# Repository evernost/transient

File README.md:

# transient
An analog synthesizer.

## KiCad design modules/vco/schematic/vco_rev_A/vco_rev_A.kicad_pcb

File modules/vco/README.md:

# VCO Module

Voltage-Controlled Module, with digital control for accurate tuning.

<!-- Example:
> This module implements a voltage-controlled low-pass filter based on a 4-pole ladder topology, intended for use in the analog signal path. -->

---

## Overview

- **Type:** VCO
- **Domain:** Analog, with Digital stabilisation
- **Status:** Work in progress

Block diagram: TODO!

---

## Features

- **Waveforms**: Sawtooth, Rectangular
- **Control**: exponential (1V/oct)
- **Inner Modulation**: up to 2 synchronised modulators to add more depth 
- **Sync**: digital input for synchronisation effect + random synchronisation

---

## Interfaces

### Inputs
| Name | Type | Range | Description |
|-----|------|-------|-------------|
| TODO | TODO | TODO |

### Outputs
| Name | Type | Description |
|------|------|-------------|
| TODO | TODO | TODO |

---

## Controls

| Control | Type | Description |
|--------|------|-------------|
| TODO | TODO | TODO |

---

## Electrical Characteristics

- **Supply voltage:** ±12V
- **Current consumption:** TBD mA
- **Signal levels:** TBD

---

## Implementation Notes

Design details, assumptions, or decisions worth remembering later.

Examples:
- Filter core based on [reference / paper / IC]
- Uses matched transistor pair for temperature stability
- Digital control smoothed with RC + oversampling

---

## Files

| File                  | Description                       |
|-----------------------|-----------------------------------|
| `vco_rev_A.pdf`       | Electrical schematic (PDF export) |
| `vco_rev_A.kicad_sch` | Schematic (KiCad 10.0.8)          |
| `vco_rev_A.kicad_pcb` | PCB layout (KiCad 10.0.8)|
| `firmware/`           | Embedded code for the VCO (STM32CubeIDE 2.1.1 - 2026) |

---

## Calibration / Tuning
> This section is TODO!

---

## Known Issues / TODO
- [ ] Create footprint for the STM32G441KB

---

## Revision History

| Revision | Date             | Notes                           |
|----------|------------------|---------------------------------|
| Rev A    | 10 November 2026 | Initial prototype               |
| Rev B    | TBA              | Added MCU for the tune control  |

---

## Related Modules

Links to other submodules in the repository:
- `../vca/`
- `../ring_modulator/`

---

## References
- Elektor FORMANT, Chapter 4 and 5

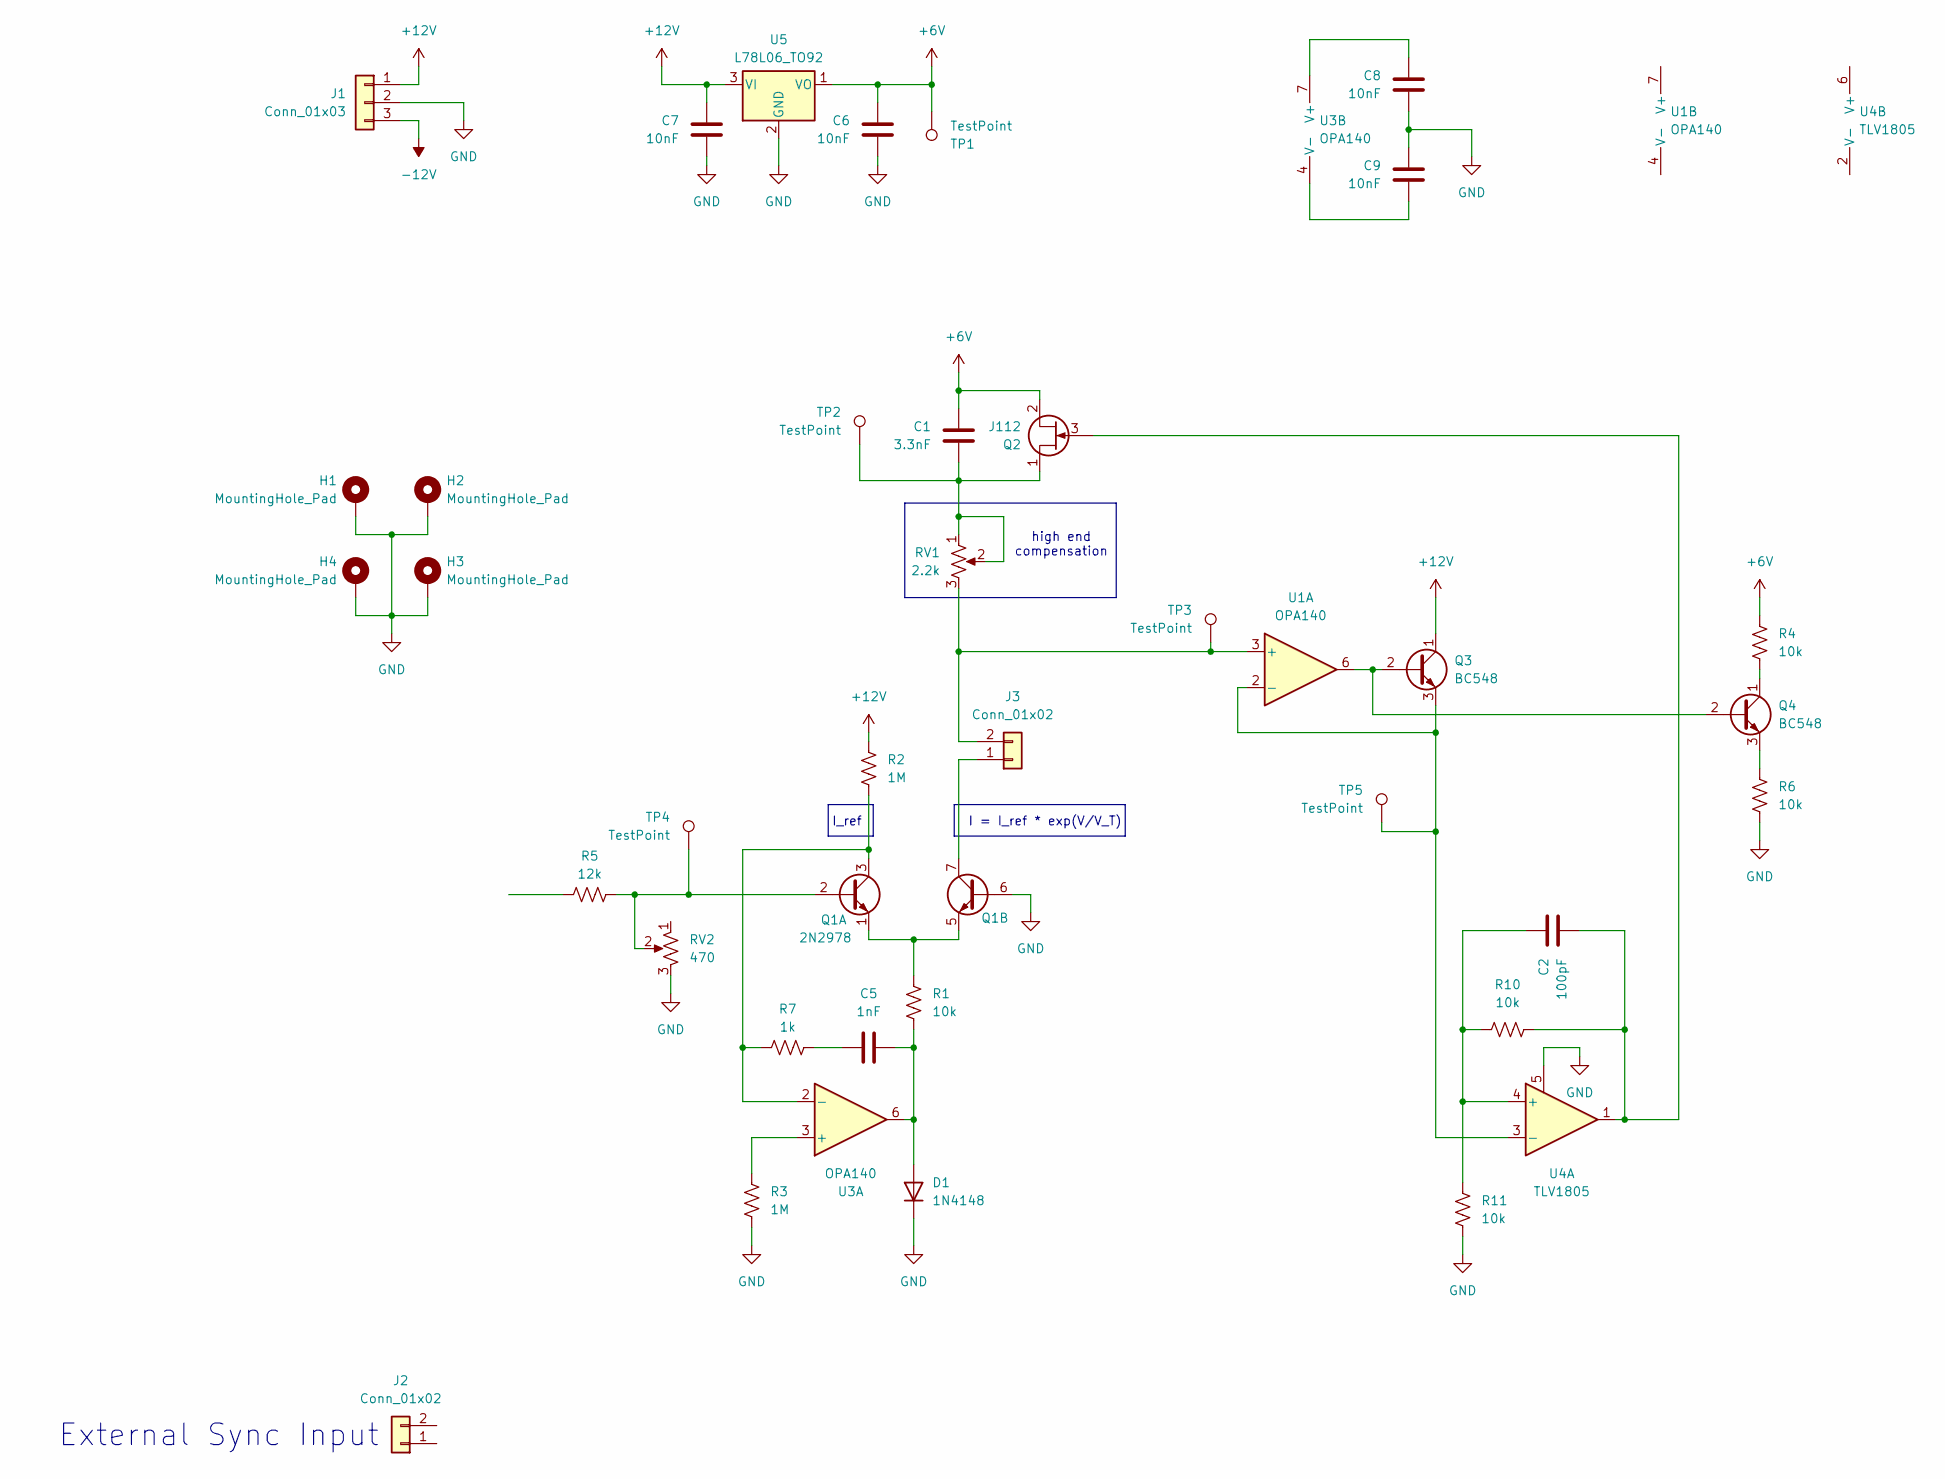
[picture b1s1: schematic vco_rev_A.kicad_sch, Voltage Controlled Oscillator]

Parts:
C1: 3.3nF; C_Rect_L7.0mm_W2.0mm_P5.00mm
C2: 100pF; C_Rect_L7.0mm_W2.0mm_P5.00mm
C5: 1nF; C_0805_2012Metric_Pad1.18x1.45mm_HandSolder
C6, C7, C8, C9: 10nF; C_Rect_L7.0mm_W2.0mm_P5.00mm
D1: 1N4148; D_DO-35_SOD27_P10.16mm_Horizontal
H1, H2, H3, H4: MountingHole_Pad; MountingHole_3.2mm_M3_Pad_Via
J1: Conn_01x03; WuerthElectronik_WR_TBL_Series_2545_1x03_P5.08mm_Horizontal
J2, J3: Conn_01x02; PinHeader_1x02_P2.54mm_Vertical
Q1: 2N2978; TO-5-6
Q2: J112; TO-92_Inline_Wide
Q3, Q4: BC548; TO-92L_Inline_Wide
R1, R4, R6, R10, R11: 10k; R_Axial_DIN0207_L6.3mm_D2.5mm_P10.16mm_Horizontal
R2, R3: 1M; R_Axial_DIN0207_L6.3mm_D2.5mm_P10.16mm_Horizontal
R5: 12k; R_Axial_DIN0207_L6.3mm_D2.5mm_P10.16mm_Horizontal
R7: 1k; R_Axial_DIN0207_L6.3mm_D2.5mm_P10.16mm_Horizontal
RV1: 2.2k; Potentiometer_Bourns_3296W_Vertical
RV2: 470; Potentiometer_Bourns_3296W_Vertical
TP1, TP2, TP3, TP4, TP5: TestPoint; TestPoint_Pad_D2.0mm
U1, U3: OPA140; VSSOP-8_3x3mm_P0.65mm
U4: TLV1805; SOT-23-6_Handsoldering
U5: L78L06_TO92; TO-92L_Inline_Wide

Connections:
+6V: C1.1, C6.1, Q2.2 (S), R4.1, TP1.1 (1_1), U5.1 (VO)
+12V: C7.1, J1.1, Q3.1 (C), R2.1, U5.3 (VI)
-12V: J1.3
GND: C6.2, C7.2, C8.2, C9.1, D1.1 (K), H1.1 (1_1), H2.1 (1_1), H3.1 (1_1), H4.1 (1_1), J1.2, Q1.6 (B2), R3.2, R6.2, R11.1, RV2.3, U4.5, U5.2 (GND)
unnamed: C5.1, R7.2
unnamed: C5.2, D1.2 (A), R1.2, U3.6
unnamed: J3.1, Q1.7 (C2)
unnamed: J3.2, RV1.3, TP3.1 (1_1), U1.3 (+)
unnamed: Q1.2 (B1), R5.2, RV2.2, TP4.1 (1_1)
unnamed: Q1.3 (C1), R2.2, R7.1, U3.2 (-)
unnamed: Q1.1 (E1), Q1.5 (E2), R1.1
unnamed: C1.2, Q2.1 (D), RV1.1, RV1.2, TP2.1 (1_1)
unnamed: C2.2, Q2.3 (G), R10.2, U4.1
unnamed: Q3.2 (B), Q4.2 (B), U1.6
unnamed: Q3.3 (E), TP5.1 (1_1), U1.2 (-), U4.3 (-)
unnamed: Q4.1 (C), R4.2
unnamed: Q4.3 (E), R6.1
unnamed: R3.1, U3.3 (+)
unnamed: C8.1, U3.7 (V+)
unnamed: C9.2, U3.4 (V-)
unnamed: C2.1, R10.1, R11.2, U4.4 (+)

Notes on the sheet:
I = I_ref * exp(V/V_T)
I_ref
high end compensation
External Sync Input

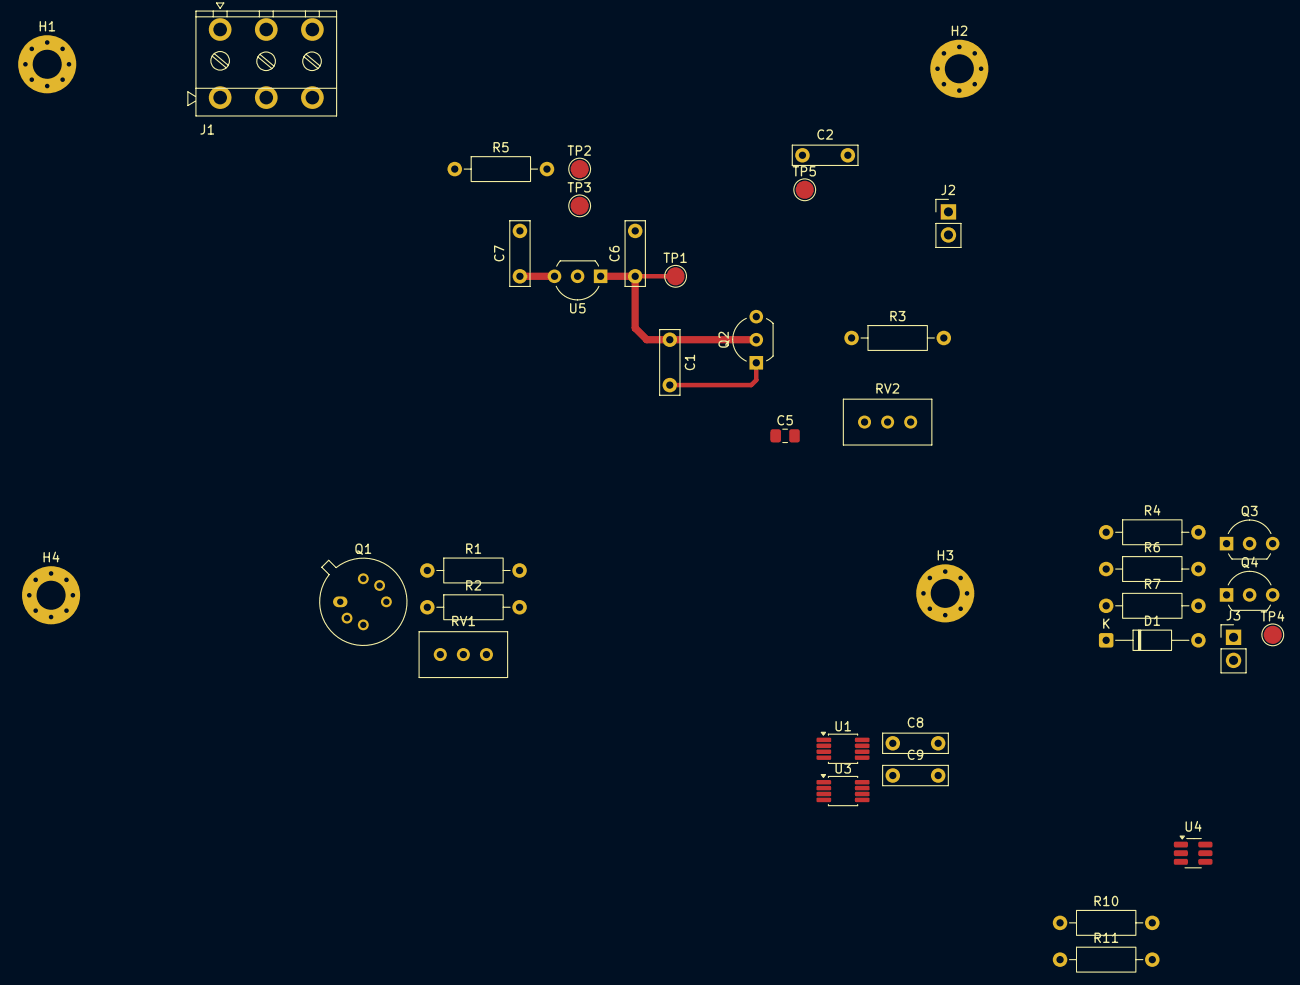
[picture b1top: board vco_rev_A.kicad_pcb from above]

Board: 2 copper layers, 39 parts (0 on the bottom side), 20 nets.

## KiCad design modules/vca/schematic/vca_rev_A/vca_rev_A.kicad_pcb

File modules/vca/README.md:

# VCA Module

A simple analog Voltage-Controlled Amplifier for audio signals.

---

## Overview

- **Type:** VCA
- **Domain:** Analog
- **Status:** Work in progress

Block diagram: TODO!

---

## Features
- **Overdrive**: the input can be overdriven on purpose to add _colors_ to the function
- **Control**: linear and logarithmic control

---

## Interfaces

### Inputs
| Name | Type | Range | Description |
|-----|------|-------|-------------|
| IN | Audio | ±1V | Input signal |
| AMP_CV | Analog | 0–5 V | Volume control |

### Outputs
| Name | Type | Description |
|------|------|-------------|
| OUT | Audio | Filtered signal |

---

## Controls

| Control | Type | Description |
|--------|------|-------------|
| Cutoff | Potentiometer | Manual cutoff frequency |

---

## Electrical Characteristics

- **Supply voltage:** ±12V
- **Current consumption:** TBD mA
- **Signal levels:** TBD

---

## Implementation Notes
Section is TODO.

---

## Files

| File                  | Description                       |
|-----------------------|-----------------------------------|
| `vca_rev_A.pdf`       | Electrical schematic (PDF export) |
| `vca_rev_A.kicad_sch` | Schematic (KiCad 10.0.8)          |
| `vca_rev_A.kicad_pcb` | PCB layout (KiCad 10.0.8)         |
| `sim/XXX.asc`         | SPICE simulation                  |

---

## Tools
Designed with KiCAD 10.0.8

### KiCAD Grid Settings

| Name   | Size    | Description        |
|--------|---------|--------------------|
| Grid 1 | 0.25 mm | PCB outline        |
| Grid 2 | 25 mil  | Parts placement    |
| Grid 3 | 25 mil  | Routing            |

**Rationale**: Grid 2 and Grid 3 were initially 50 mil, but turned out to be too coarse for precise tracks.

### KiCAD Track settings

| Name    | Size   | Description                |
|---------|--------|----------------------------|
| Class 1 | 500 um | Regular traces (signal)    |
| Class 2 | 800 um | Power traces               |

---

## Calibration / Tuning
No calibration required.

---

## Known Issues / TODO

- [ ] TODO

---

## Revision History

| Revision | Date | Notes |
|--------|------|-------|
| Rev A | YYYY-MM-DD | Initial prototype |

---

## Related Modules

Links to other submodules in the repository:
- `../vca/`
- `../ring_modulator/`

---

## References

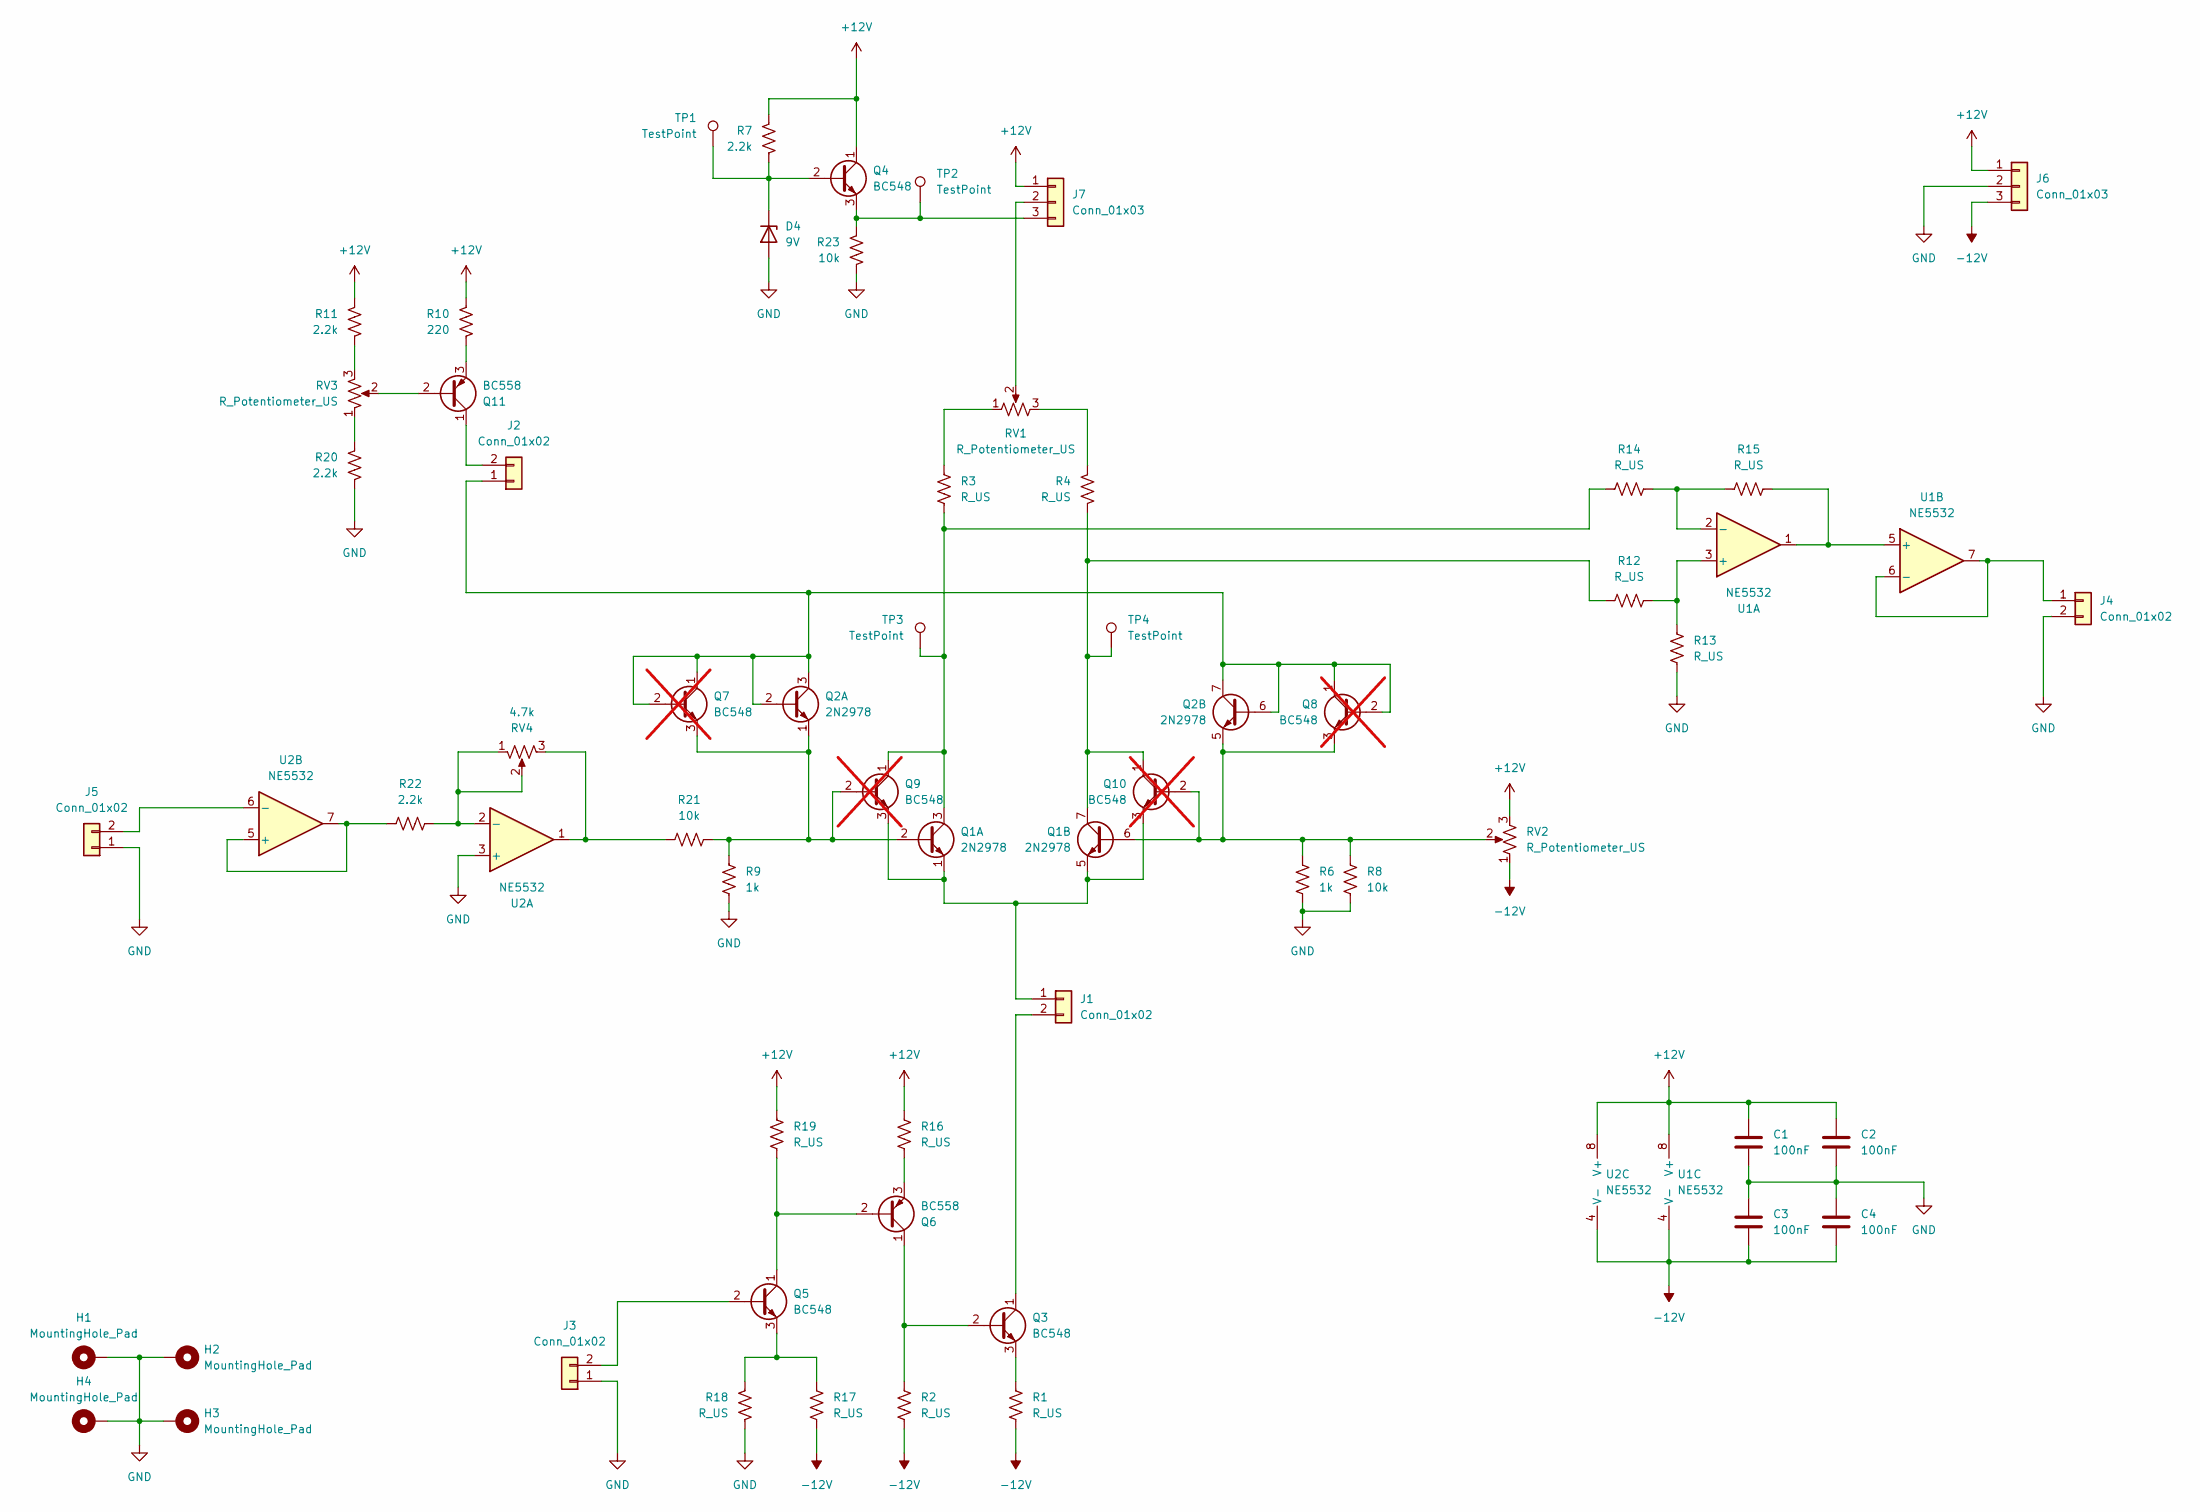
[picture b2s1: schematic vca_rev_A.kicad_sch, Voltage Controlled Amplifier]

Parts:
C1, C2, C3, C4: 100nF; C_Rect_L7.0mm_W2.0mm_P5.00mm
D4: 9V; D_DO-41_SOD81_P10.16mm_Horizontal
H1, H2, H3, H4: MountingHole_Pad; MountingHole_3.2mm_M3_Pad_Via
J1, J2, J3, J4, J5: Conn_01x02; PinHeader_1x02_P2.54mm_Vertical
J6: Conn_01x03; WuerthElectronik_WR_TBL_Series_2545_1x03_P5.08mm_Horizontal
J7: Conn_01x03; PinSocket_1x03_P2.54mm_Vertical
Q1, Q2: 2N2978; TO-5-6
Q3, Q4, Q5: BC548; TO-92L_Inline_Wide
Q6, Q11: BC558; TO-92L_Inline_Wide
Q7, Q8, Q9, Q10: BC548; TO-92L_Inline_Wide; not fitted
R1, R2, R3, R4, R12, R13, R14, R15, R16, R17, R18, R19: R_US; R_Axial_DIN0207_L6.3mm_D2.5mm_P10.16mm_Horizontal
R6, R9: 1k; R_Axial_DIN0207_L6.3mm_D2.5mm_P10.16mm_Horizontal
R7, R11, R20, R22: 2.2k; R_Axial_DIN0207_L6.3mm_D2.5mm_P10.16mm_Horizontal
R8, R21, R23: 10k; R_Axial_DIN0207_L6.3mm_D2.5mm_P10.16mm_Horizontal
R10: 220; R_Axial_DIN0207_L6.3mm_D2.5mm_P10.16mm_Horizontal
RV1, RV2, RV3: R_Potentiometer_US; Potentiometer_Bourns_3296W_Vertical
RV4: 4.7k; Potentiometer_Bourns_3296W_Vertical
TP1, TP2, TP3, TP4: TestPoint; TestPoint_Pad_D2.0mm
U1, U2: NE5532; SOIC-8_5.3x6.2mm_P1.27mm

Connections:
+12V: C1.1, C2.1, J6.1, J7.1, Q4.1 (C), R7.1, R10.1, R11.1, R16.1, R19.1, RV2.3, U1.8 (V+), U2.8 (V+)
-12V: C3.2, C4.2, J6.3, R1.2, R2.2, R17.2, RV2.1, U1.4 (V-), U2.4 (V-)
GND: C1.2, C2.2, C3.1, C4.1, D4.2 (A), H1.1 (1_1), H2.1 (1_1), H3.1 (1_1), H4.1 (1_1), J3.1, J4.2, J5.1, J6.2, R6.2, R8.2, R9.2, R13.2, R18.2, R20.2, R23.2, U2.3 (+)
unnamed: D4.1 (K), Q4.2 (B), R7.2, TP1.1 (1_1)
unnamed: J1.1, Q1.1 (E1), Q1.5 (E2), Q9.3 (E), Q10.3 (E)
unnamed: J1.2, Q3.1 (C)
unnamed: J2.1, Q2.2 (B1), Q2.3 (C1), Q2.6 (B2), Q2.7 (C2), Q7.1 (C), Q7.2 (B), Q8.1 (C), Q8.2 (B)
unnamed: J2.2, Q11.1 (C)
unnamed: J3.2, Q5.2 (B)
unnamed: J4.1, U1.6 (-), U1.7
unnamed: J5.2, U2.6 (-)
unnamed: J7.2, RV1.2
unnamed: J7.3, Q4.3 (E), R23.1, TP2.1 (1_1)
unnamed: Q1.2 (B1), Q2.1 (E1), Q7.3 (E), Q9.2 (B), R9.1, R21.2
unnamed: Q1.3 (C1), Q9.1 (C), R3.2, R14.1, TP3.1 (1_1)
unnamed: Q3.2 (B), Q6.1 (C), R2.1
unnamed: Q3.3 (E), R1.1
unnamed: Q5.1 (C), Q6.2 (B), R19.2
unnamed: Q5.3 (E), R17.1, R18.1
unnamed: Q6.3 (E), R16.2
unnamed: Q1.6 (B2), Q2.5 (E2), Q8.3 (E), Q10.2 (B), R6.1, R8.1, RV2.2
unnamed: Q1.7 (C2), Q10.1 (C), R4.2, R12.1, TP4.1 (1_1)
unnamed: Q11.2 (B), RV3.2
unnamed: Q11.3 (E), R10.2
unnamed: R3.1, RV1.1
unnamed: R4.1, RV1.3
unnamed: R11.2, RV3.3
unnamed: R20.1, RV3.1
unnamed: R21.1, RV4.3, U2.1
unnamed: R12.2, R13.1, U1.3 (+)
unnamed: R14.2, R15.1, U1.2 (-)
unnamed: R15.2, U1.1, U1.5 (+)
unnamed: R22.2, RV4.1, RV4.2, U2.2 (-)
unnamed: R22.1, U2.5 (+), U2.7

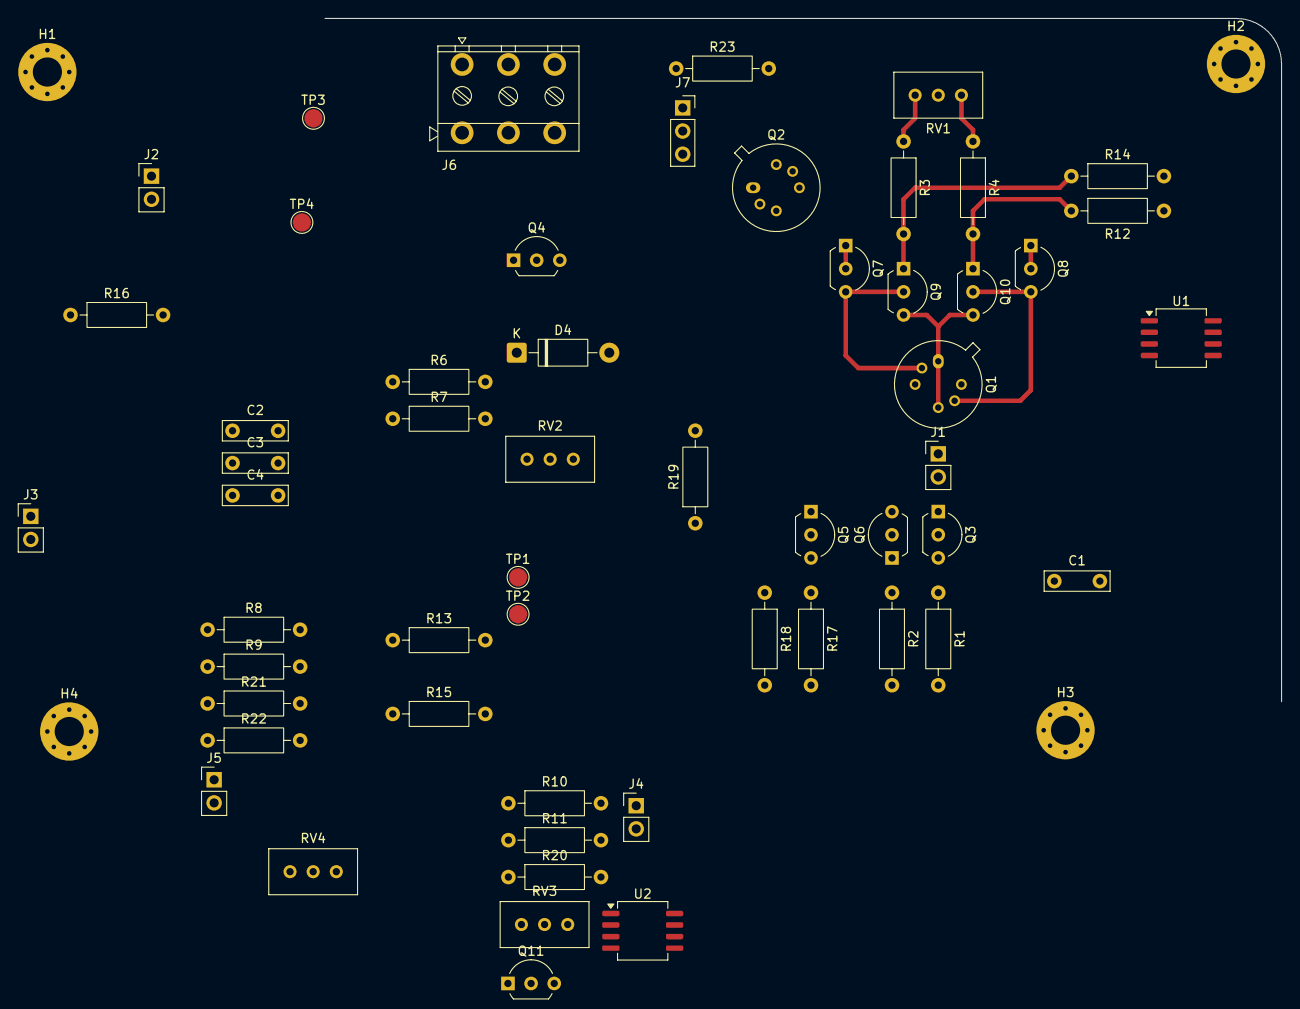
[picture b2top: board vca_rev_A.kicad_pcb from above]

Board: 2 copper layers, 59 parts (0 on the bottom side), 34 nets.

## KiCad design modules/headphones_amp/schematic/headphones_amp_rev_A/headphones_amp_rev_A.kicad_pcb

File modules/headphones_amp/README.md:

# Headphones Amplifier

Output stage module for headphones with gain and balance control.

---

## Overview

- **Type:** Amplifier
- **Domain:** Analog
- **Status:** Work in progress

Block diagram: TODO!

---

## Features
- Stereo amplifier
- Balance knob
- Volume knob
- Single power supply (+12V)
- Input impedance: TBD Ohms
- Output impedance: 32 Ohms
- Overload indicator (excessive power)

---

## Interfaces

### Inputs
| Name | Type | Range | Description |
|-----|------|-------|-------------|
| IN | Audio | ±1V | Input signal |
| AMP_CV | Analog | 0–5 V | Volume control |

### Outputs
| Name | Type | Description |
|------|------|-------------|
| OUT | Audio | Filtered signal |

---

## Controls

| Control | Type | Description |
|--------|------|-------------|
| Cutoff | Potentiometer | Manual cutoff frequency |
| Resonance | Potentiometer | Feedback amount |

---

## Electrical Characteristics

- **Supply voltage:** +12V
- **Current consumption:** TBD mA
- **Signal levels:** TBD

---

## Implementation Notes
Section is TODO.

---

## Files

| File                              | Description                           |
|-----------------------------------|---------------------------------------|
| `headphones_amp_rev_A.pdf`        | Electrical schematic (PDF export)     |
| `headphones_amp_rev_A.kicad_sch`  | Schematic (KiCad 10.0.8)              |
| `headphones_amp_rev_A.kicad_pcb`  | PCB layout (KiCad 10.0.8)             |
| `sim/XXX.asc`                     | SPICE simulation of the final stage   |

---

## Tools
Designed with KiCAD 10.0.8

### KiCAD Grid Settings

| Name   | Size    | Description        |
|--------|---------|--------------------|
| Grid 1 | 0.25 mm | PCB outline        |
| Grid 2 | 25 mil  | Parts placement    |
| Grid 3 | 25 mil  | Routing            |

**Rationale**: Grid 2 and Grid 3 were initially 50 mil, but turned out to be too coarse for precise tracks.

### KiCAD Track settings

| Name    | Size   | Description                |
|---------|--------|----------------------------|
| Class 1 | 500 um | Regular traces (signal)    |
| Class 2 | 800 um | Power traces               |

---

## Calibration / Tuning
- Tune the bias voltage on $Q_5$ and $Q_{11}$
- Tune the quiescent current 
- Tune the overload threshold

---

## Known Issues / TODO

- [ ] Make the bias point higher: 1.6V might clip too early
- [ ] Add a reverse polarity protection

---

## Revision History

| Revision | Date | Notes |
|--------|------|-------|
| Rev A | YYYY-MM-DD | Initial prototype |
| Rev B | YYYY-MM-DD | Fixed grounding issue |

---

## Related Modules

Links to other submodules in the repository:
- `../vca/`
- `../ring_modulator/`

---

## References
- Elektor Voiced/Devoiced detector, April 1981 p.32-33

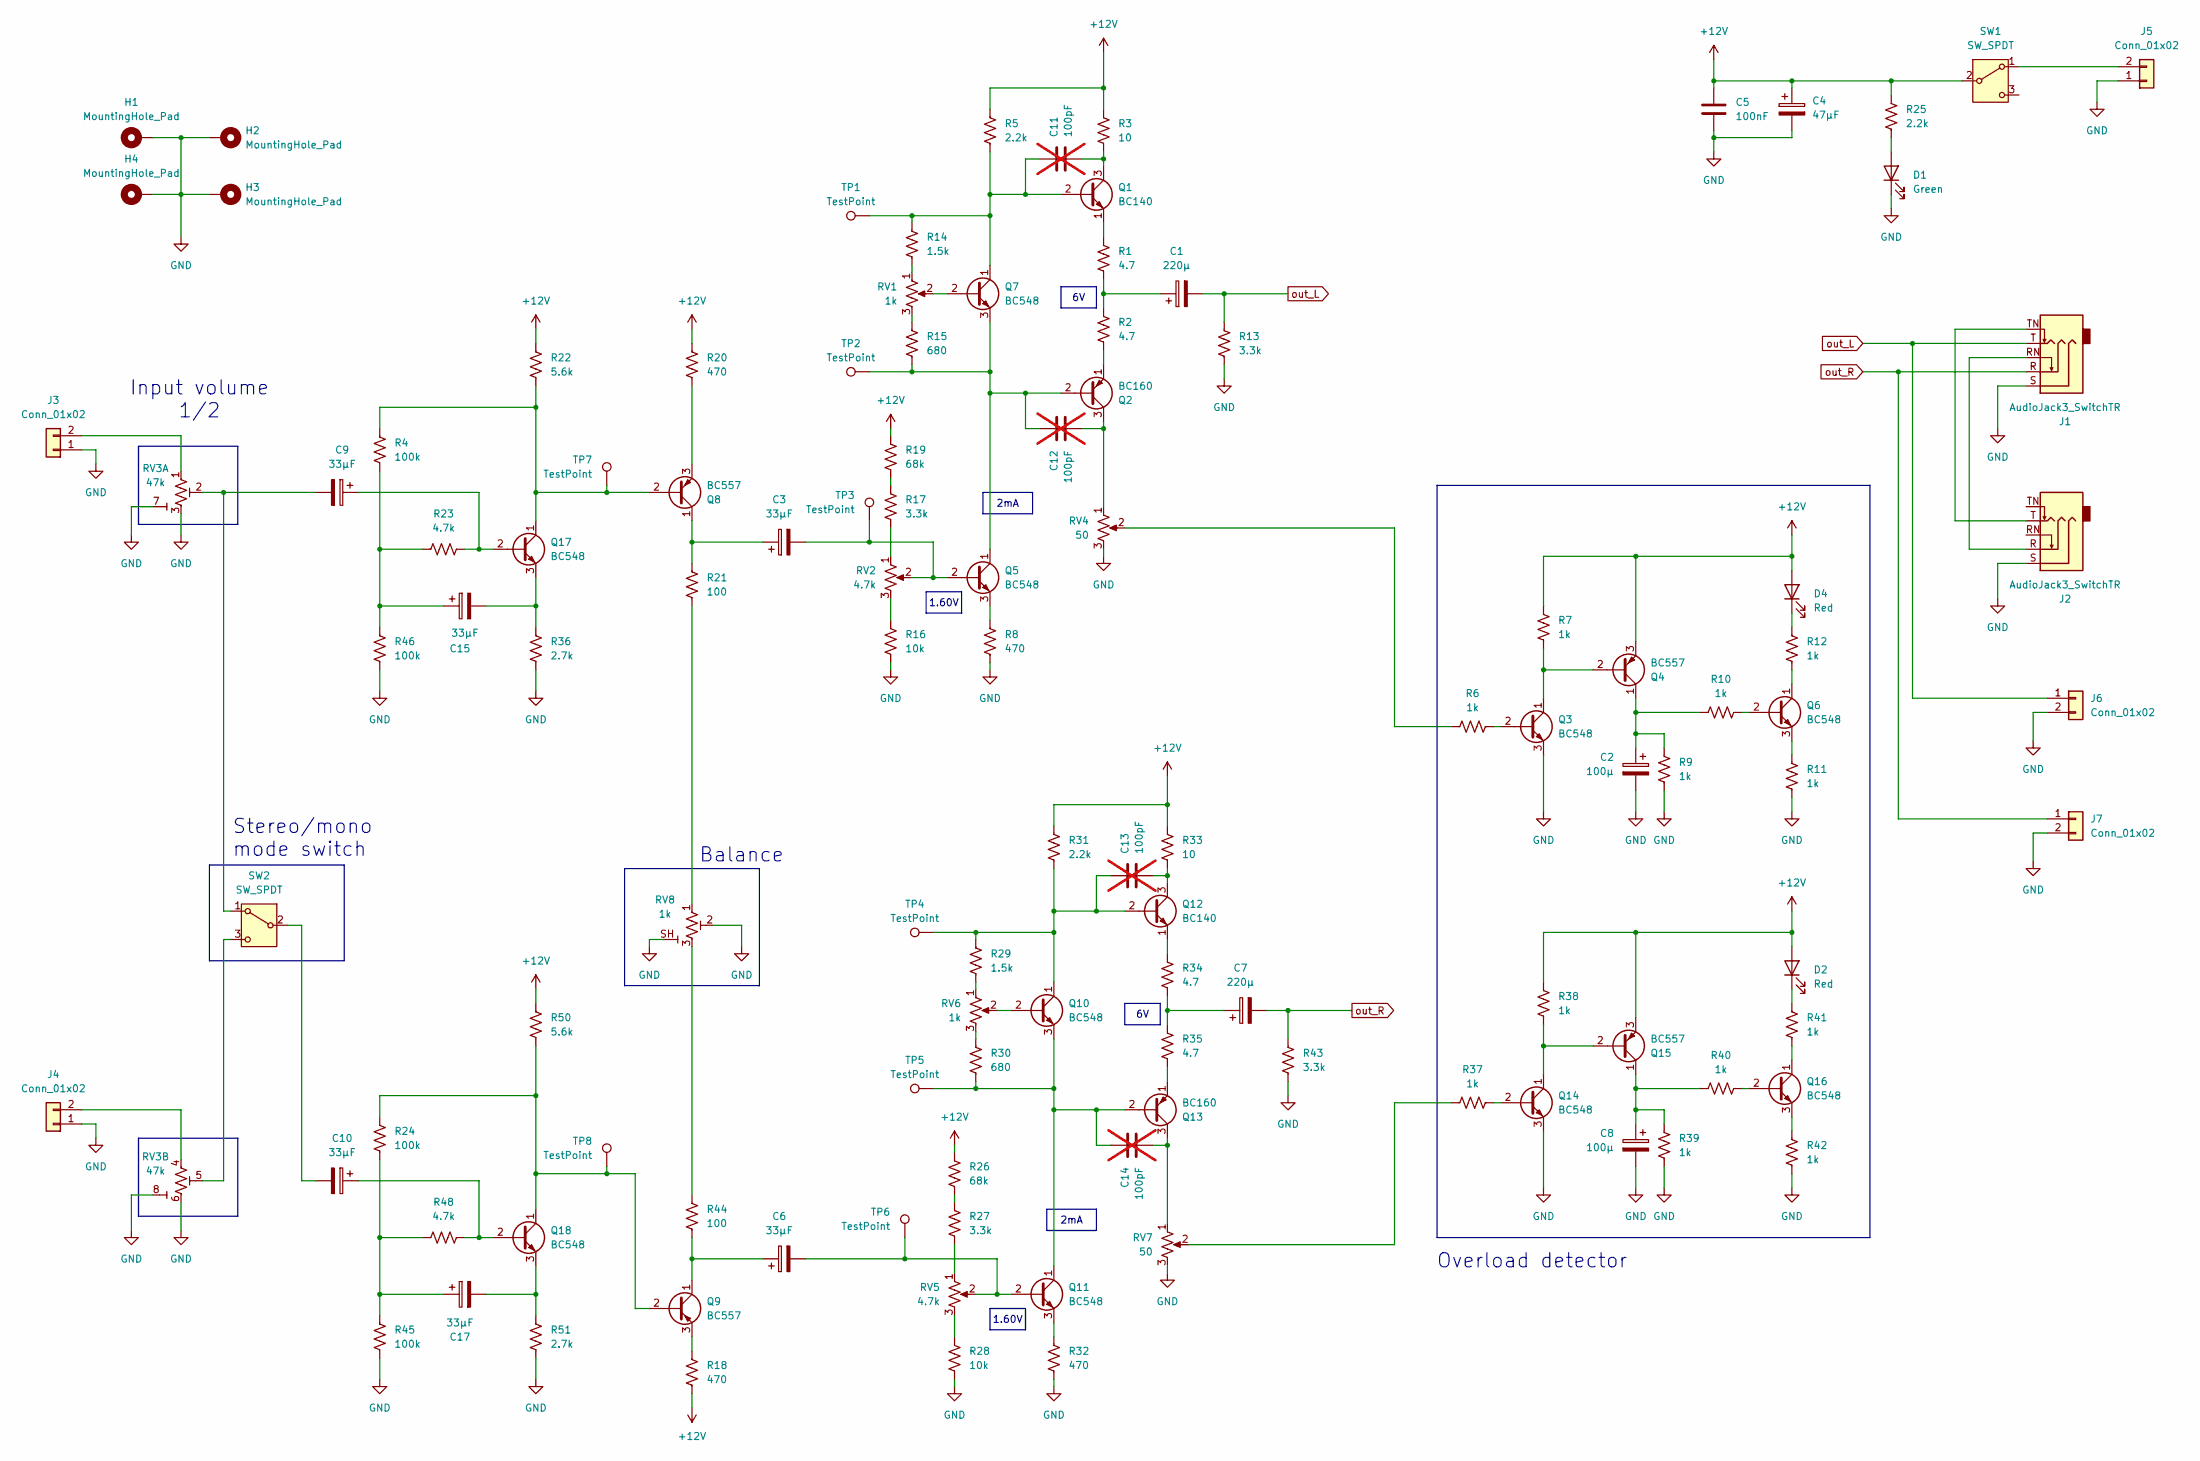
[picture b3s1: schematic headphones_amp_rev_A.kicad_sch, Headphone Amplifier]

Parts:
C1, C7: 220µ; CP_Radial_D10.0mm_P5.00mm
C2, C8: 100µ; CP_Radial_D10.0mm_P5.00mm
C3, C6, C9, C10, C15, C17: 33µF; CP_Radial_D10.0mm_P5.00mm
C4: 47µF; CP_Radial_D10.0mm_P5.00mm
C5: 100nF; C_Rect_L7.0mm_W2.0mm_P5.00mm
C11, C12, C13, C14: 100pF; C_Rect_L7.0mm_W2.0mm_P5.00mm; not fitted
D1: Green; LED_D3.0mm
D2, D4: Red; LED_D3.0mm
H1, H2, H3, H4: MountingHole_Pad; MountingHole_3.2mm_M3_Pad_Via
J1: AudioJack3_SwitchTR; Jack_6.35mm_Neutrik_NRJ6HM-1-PRE_Horizontal
J2: AudioJack3_SwitchTR; Jack_3.5mm_CUI_SJ1-3515N_Horizontal
J3, J4, J6, J7: Conn_01x02; WuerthElectronik_WR_TBL_Series_2109_1x02_P2.54mm_Horizontal
J5: Conn_01x02; WuerthElectronik_WR_TBL_Series_2545_1x02_P5.08mm_Horizontal
Q1, Q12: BC140; TO-39-3
Q2, Q13: BC160; TO-39-3
Q3, Q5, Q6, Q7, Q10, Q11, Q14, Q16, Q17, Q18: BC548; TO-92L_Inline_Wide
Q4, Q8, Q9, Q15: BC557; TO-92L_Inline_Wide
R1, R2, R34, R35: 4.7; R_Axial_DIN0207_L6.3mm_D2.5mm_P10.16mm_Horizontal
R3, R33: 10; R_Axial_DIN0207_L6.3mm_D2.5mm_P10.16mm_Horizontal
R4, R24, R45, R46: 100k; R_Axial_DIN0207_L6.3mm_D2.5mm_P10.16mm_Horizontal
R5, R25, R31: 2.2k; R_Axial_DIN0207_L6.3mm_D2.5mm_P10.16mm_Horizontal
R6, R7, R9, R10, R11, R12, R37, R38, R39, R40, R41, R42: 1k; R_Axial_DIN0207_L6.3mm_D2.5mm_P10.16mm_Horizontal
R8, R18, R20, R32: 470; R_Axial_DIN0207_L6.3mm_D2.5mm_P10.16mm_Horizontal
R13, R17, R27, R43: 3.3k; R_Axial_DIN0207_L6.3mm_D2.5mm_P10.16mm_Horizontal
R14, R29: 1.5k; R_Axial_DIN0207_L6.3mm_D2.5mm_P10.16mm_Horizontal
R15, R30: 680; R_Axial_DIN0207_L6.3mm_D2.5mm_P10.16mm_Horizontal
R16, R28: 10k; R_Axial_DIN0207_L6.3mm_D2.5mm_P10.16mm_Horizontal
R19, R26: 68k; R_Axial_DIN0207_L6.3mm_D2.5mm_P10.16mm_Horizontal
R21, R44: 100; R_Axial_DIN0207_L6.3mm_D2.5mm_P10.16mm_Horizontal
R22, R50: 5.6k; R_Axial_DIN0207_L6.3mm_D2.5mm_P10.16mm_Horizontal
R23, R48: 4.7k; R_Axial_DIN0207_L6.3mm_D2.5mm_P10.16mm_Horizontal
R36, R51: 2.7k; R_Axial_DIN0207_L6.3mm_D2.5mm_P10.16mm_Horizontal
RV1, RV6: 1k; Potentiometer_Bourns_3296W_Vertical
RV2, RV5: 4.7k; Potentiometer_Bourns_3296W_Vertical
RV3: 47k; Potentiometer_Bourns_PTV112-4_Dual_Vertical
RV4, RV7: 50; Potentiometer_Bourns_3296W_Vertical
RV8: 1k; Potentiometer_Bourns_PTV09A-4_Single_Vertical
SW1, SW2: SW_SPDT; SW_CIT_ANT13_SPDT_Straight
TP1, TP2, TP3, TP4, TP5, TP6, TP7, TP8: TestPoint; TestPoint_Pad_D2.0mm

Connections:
+12V: C4.1, C5.1, D2.2 (A), D4.2 (A), Q4.3 (E), Q15.3 (E), R3.1, R5.1, R7.1, R18.2, R19.2, R20.1, R22.1, R25.1, R26.2, R31.1, R33.1, R38.1, R50.1, SW1.2
GND: C2.2, C4.2, C5.2, C8.2, D1.1 (K), H1.1 (1_1), H2.1 (1_1), H3.1 (1_1), H4.1 (1_1), J1.S, J2.S, J3.1, J4.1, J5.1, J6.2, J7.2, Q3.3 (E), Q14.3 (E), R8.2, R9.2, R11.2, R13.2, R16.2, R28.2, R32.2, R36.2, R39.2, R42.2, R43.2, R45.2, R46.2, R51.2, RV3.3 (B), RV3.6 (B), RV3.7 (SH1), RV3.8 (SH2), RV4.3, RV7.3, RV8.2 (W), RV8.SH
unnamed: C1.1, R1.2, R2.1
unnamed: C7.1, R34.2, R35.1
unnamed: C10.2, SW2.2
unnamed: C15.1, R4.2, R23.1, R46.1
unnamed: C17.1, R24.2, R45.1, R48.1
unnamed: D1.2 (A), R25.2
unnamed: D2.1 (K), R41.1
unnamed: D4.1 (K), R12.1
unnamed: J1.RN, J2.R
unnamed: J1.TN, J2.T
unnamed: J3.2, RV3.1 (A)
unnamed: J4.2, RV3.4 (A)
unnamed: J5.2, SW1.1
unnamed: C11.1, Q1.2 (B), Q7.1 (C), R5.2, R14.1, TP1.1 (1_1)
unnamed: C11.2, Q1.3 (C), R3.2
unnamed: Q1.1 (E), R1.1
unnamed: C12.1, Q2.2 (B), Q5.1 (C), Q7.3 (E), R15.2, TP2.1 (1_1)
unnamed: C12.2, Q2.3 (C), RV4.1
unnamed: Q2.1 (E), R2.2
unnamed: Q3.2 (B), R6.2
unnamed: Q3.1 (C), Q4.2 (B), R7.2
unnamed: C2.1, Q4.1 (C), R9.1, R10.1
unnamed: C3.2, Q5.2 (B), RV2.2, TP3.1 (1_1)
unnamed: Q5.3 (E), R8.1
unnamed: Q6.2 (B), R10.2
unnamed: Q6.1 (C), R12.2
unnamed: Q6.3 (E), R11.1
unnamed: Q7.2 (B), RV1.2
unnamed: C3.1, Q8.1 (C), R21.1
unnamed: Q8.3 (E), R20.2
unnamed: C6.1, Q9.1 (C), R44.2
unnamed: Q9.3 (E), R18.1
unnamed: Q10.2 (B), RV6.2
unnamed: C13.1, Q10.1 (C), Q12.2 (B), R29.1, R31.2, TP4.1 (1_1)
unnamed: C14.1, Q10.3 (E), Q11.1 (C), Q13.2 (B), R30.2, TP5.1 (1_1)
unnamed: C6.2, Q11.2 (B), RV5.2, TP6.1 (1_1)
unnamed: Q11.3 (E), R32.1
unnamed: C13.2, Q12.3 (C), R33.2
unnamed: Q12.1 (E), R34.1
unnamed: C14.2, Q13.3 (C), RV7.1
unnamed: Q13.1 (E), R35.2
unnamed: Q14.2 (B), R37.2
unnamed: Q14.1 (C), Q15.2 (B), R38.2
unnamed: C8.1, Q15.1 (C), R39.1, R40.1
unnamed: Q16.2 (B), R40.2
unnamed: Q16.1 (C), R41.2
unnamed: Q16.3 (E), R42.1
unnamed: C9.1, Q17.2 (B), R23.2
unnamed: Q8.2 (B), Q17.1 (C), R4.1, R22.2, TP7.1 (1_1)
unnamed: C15.2, Q17.3 (E), R36.1
unnamed: C10.1, Q18.2 (B), R48.2
unnamed: Q9.2 (B), Q18.1 (C), R24.1, R50.2, TP8.1 (1_1)
unnamed: C17.2, Q18.3 (E), R51.1
unnamed: R6.1, RV4.2
unnamed: R14.2, RV1.1
unnamed: R15.1, RV1.3
unnamed: R16.1, RV2.3
unnamed: R17.1, R19.1
unnamed: R17.2, RV2.1
unnamed: R26.1, R27.1
unnamed: R27.2, RV5.1
unnamed: R28.1, RV5.3
unnamed: R29.2, RV6.1
unnamed: R30.1, RV6.3
unnamed: R37.1, RV7.2
unnamed: C9.2, RV3.2 (W), SW2.1
unnamed: RV3.5 (W), SW2.3
unnamed: R21.2, RV8.1 (A)
unnamed: R44.1, RV8.3 (B)
out_L: C1.2, J1.T, J6.1, R13.1
out_R: C7.2, J1.R, J7.1, R43.1

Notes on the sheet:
Stereo/mono mode switch
Overload detector
Input volume 1/2
Balance
1.60V
2mA

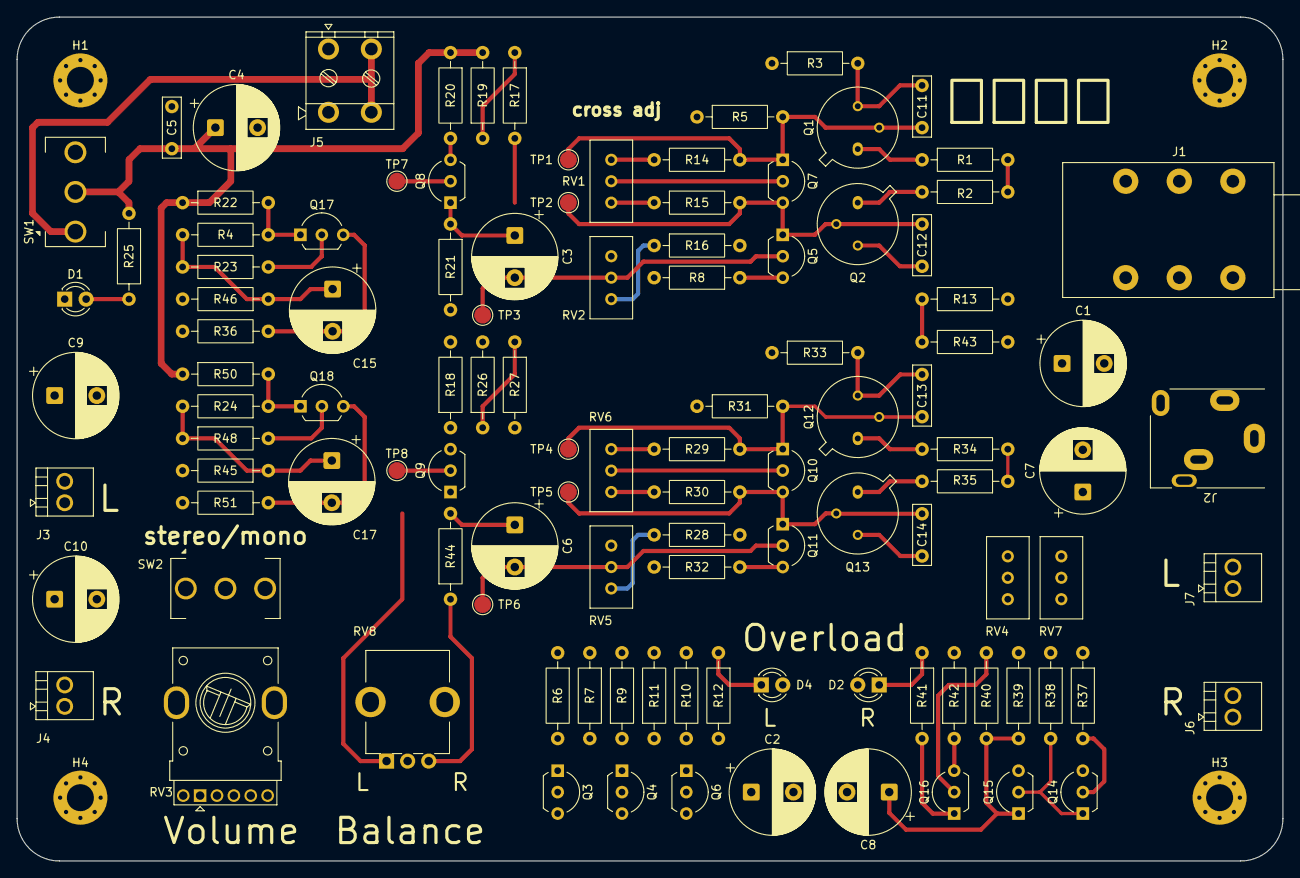
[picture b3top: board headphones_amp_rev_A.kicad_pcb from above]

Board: 2 copper layers, 150.0 x 100.0 mm, 115 parts (0 on the bottom side), 73 nets.

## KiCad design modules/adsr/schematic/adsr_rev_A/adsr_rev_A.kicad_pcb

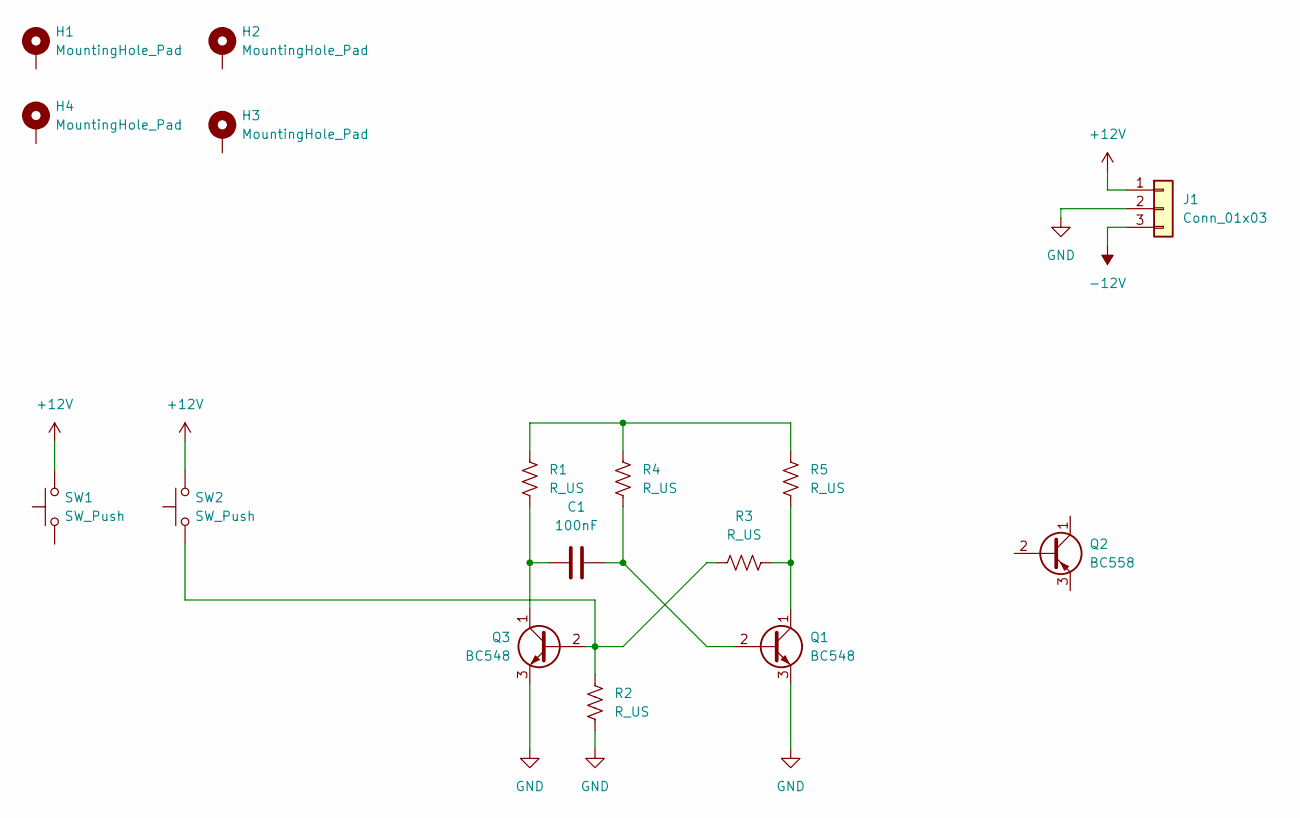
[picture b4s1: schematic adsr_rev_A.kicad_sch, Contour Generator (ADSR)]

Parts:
C1: 100nF; C_Rect_L7.0mm_W2.0mm_P5.00mm
H1, H2, H3, H4: MountingHole_Pad; MountingHole_3.2mm_M3_Pad_Via
J1: Conn_01x03; WuerthElectronik_WR_TBL_Series_2545_1x03_P5.08mm_Horizontal
Q1, Q3: BC548; TO-92L_Inline_Wide
Q2: BC558; TO-92L_Inline_Wide
R1, R2, R3, R4, R5: R_US; R_Axial_DIN0207_L6.3mm_D2.5mm_P10.16mm_Horizontal
SW1, SW2: SW_Push; SW_Push_1P1T_NO_CK_KSC6xxG

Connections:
+12V: J1.1, SW1.2 (2_2), SW2.2
-12V: J1.3
GND: J1.2, Q1.3 (E), Q3.3 (E), R2.2
unnamed: C1.2, Q1.2 (B), R4.2
unnamed: Q1.1 (C), R3.2, R5.2
unnamed: Q3.2 (B), R2.1, R3.1, SW2.1
unnamed: C1.1, Q3.1 (C), R1.2
unnamed: R1.1, R4.1, R5.1

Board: 2 copper layers, 16 parts (0 on the bottom side), 7 nets, no tracks yet.
